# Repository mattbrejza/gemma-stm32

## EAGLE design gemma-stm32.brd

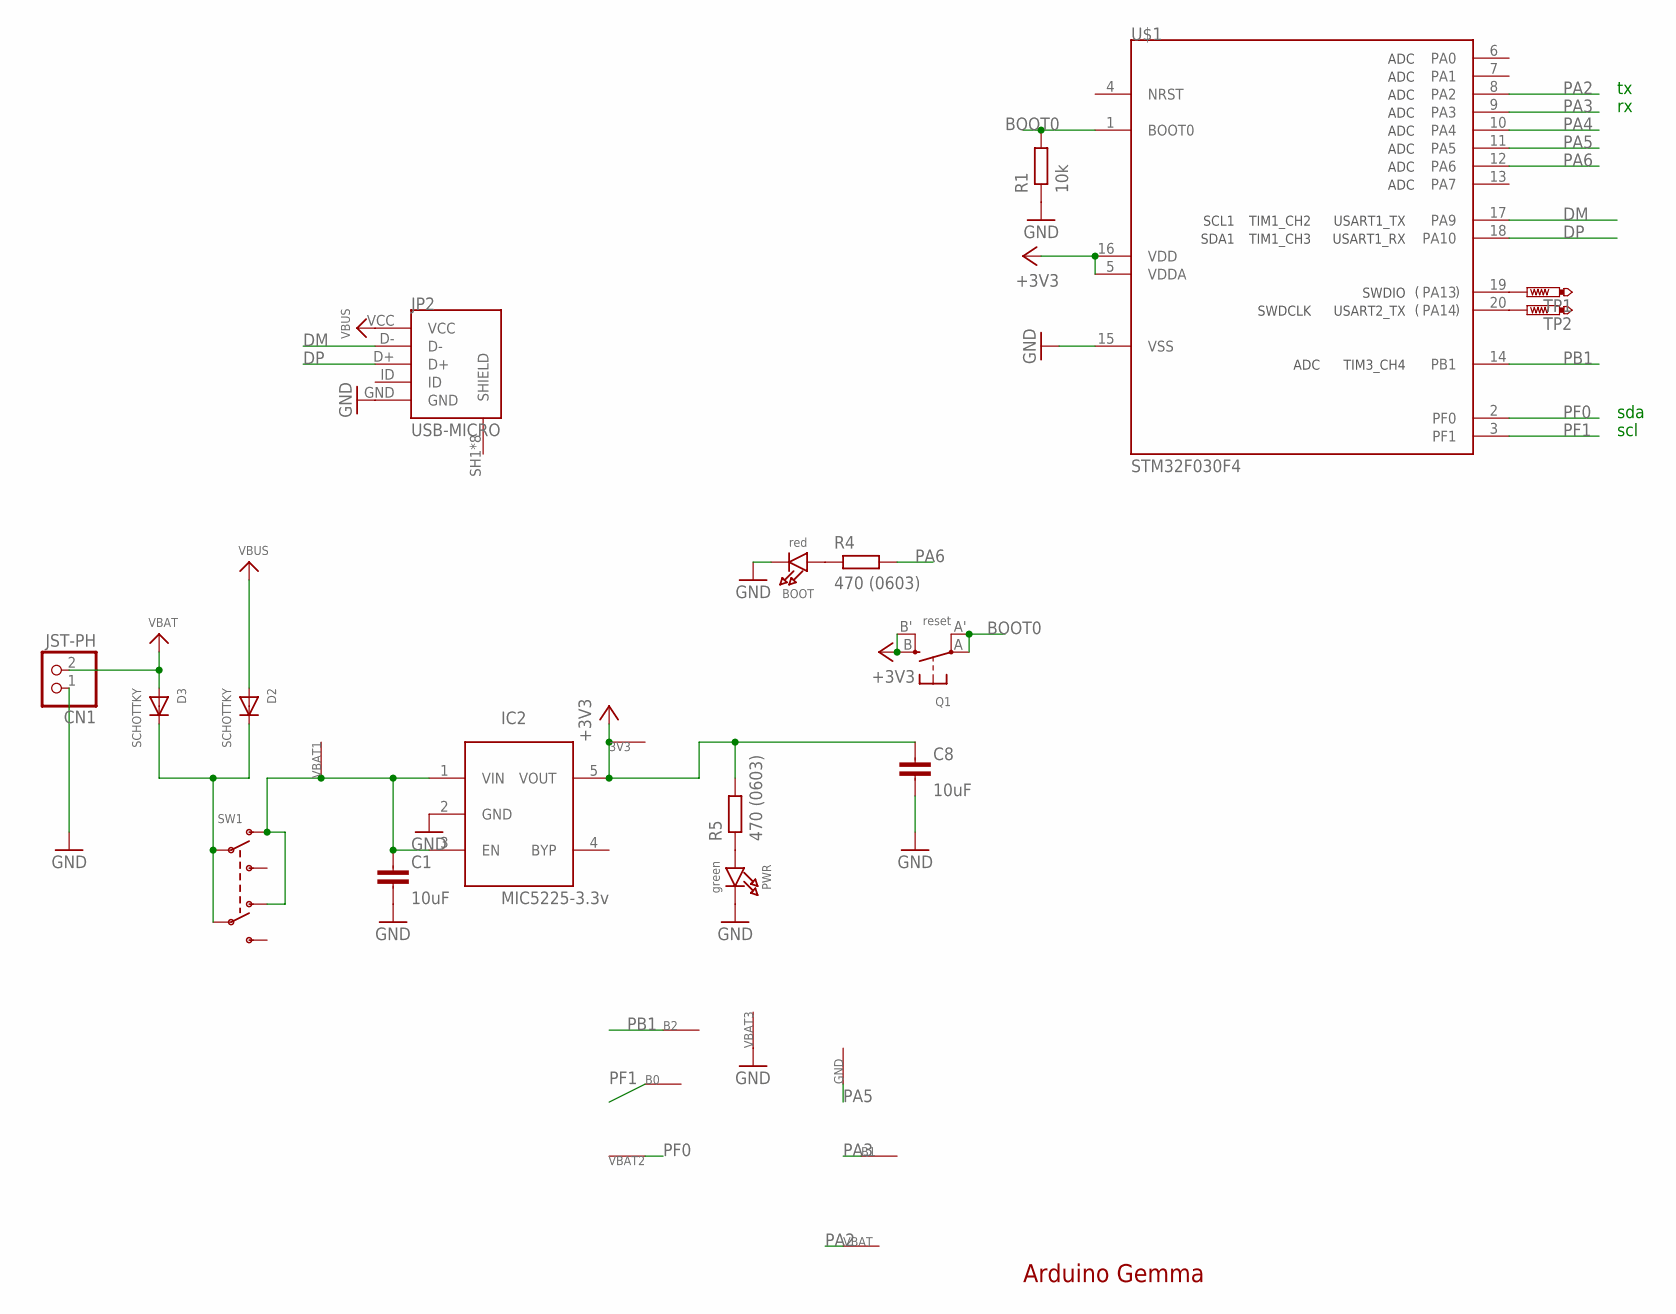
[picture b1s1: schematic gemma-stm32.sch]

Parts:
3V3: SEWTAP-2.0IN; SEWINGTAP_2.0
B0, B1: SEWTAP-2.0IN; SEWINGTAP_2.0
B2: SEWTAP2.0-L; SEWINGTAP_2.0_NARROW_L
BOOT: red; CHIPLED_0805_NOOUTLINE
C1, C8: 10uF; C0603-L
CN1: JST-PH; JSTPH2
D2, D3: SCHOTTKY; SOD-123FL
GND: SEWTAP-2.0IN; SEWINGTAP_2.0
IC2: MIC5225-3.3v; SOT23-5L
JP2: USB-MICRO; MOLEX_47589-0001
PWR: green; CHIPLED_0805_NOOUTLINE
Q1: reset; BTN_KMR2_4.6X2.8
R1: 10k; R0603-L
R4, R5: 470 (0603); R0603-L
SW1: SWITCH_DPDTEG1390; EG1390
TP1, TP2: PTR1TP08R; TP08R
U$1: STM32F030F4; TSSOP20
VBAT, VBAT2: SEWTAP-2.0IN; SEWINGTAP_2.0
VBAT1: SEWTAP; SEWINGTAP_2.0_ONESIDE
VBAT3: SEWTAP2.0-R; SEWINGTAP_2.0_NARROW_R

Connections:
+3V3: 3V3.P$1, C8.1, IC2.5 (VOUT), Q1.B (S), Q1.B' (S1), R5.2, U$1.5 (VDDA), U$1.16 (VDD)
BOOT0: Q1.A, Q1.A' (P1), R1.2, U$1.1 (BOOT0)
DM: JP2.D-, U$1.17 (PA9)
DP: JP2.D+, U$1.18 (PA10)
GND: BOOT.C, C1.2, C8.2, CN1.1, IC2.2 (GND), JP2.GND, PWR.C, R1.1, U$1.15 (VSS), VBAT3.P$1
unnamed: TP1.TP, U$1.19 (PA13)
unnamed: TP2.TP, U$1.20 (PA14)
unnamed: BOOT.A, R4.1
unnamed: C1.1, IC2.1 (VIN), IC2.3 (EN), SW1.O1, SW1.O2, VBAT1.P$1
unnamed: PWR.A, R5.1
unnamed: D2.C, D3.C, SW1.P1, SW1.P2
PA2: U$1.8 (PA2), VBAT.P$1
PA3: B1.P$1, U$1.9 (PA3)
PA4: U$1.10 (PA4)
PA5: GND.P$1, U$1.11 (PA5)
PA6: R4.2, U$1.12 (PA6)
PB1: B2.P$1, U$1.14 (PB1)
PF0: U$1.2 (PF0), VBAT2.P$1
PF1: B0.P$1, U$1.3 (PF1)
VBAT: CN1.2, D3.A
VBUS: D2.A, JP2.VCC

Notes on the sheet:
Arduino Gemma
sda
scl

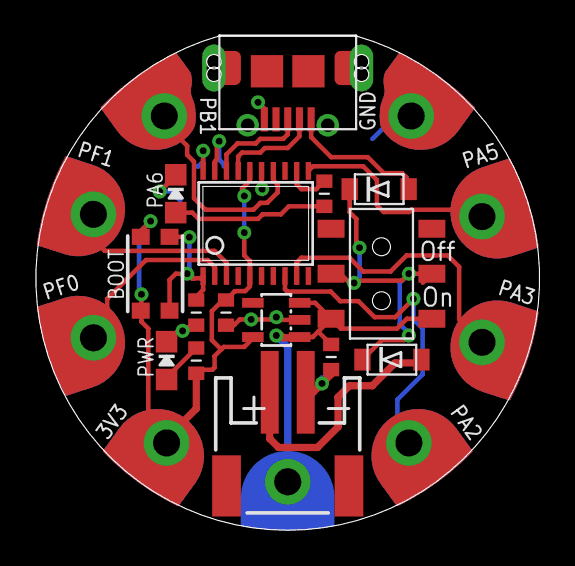
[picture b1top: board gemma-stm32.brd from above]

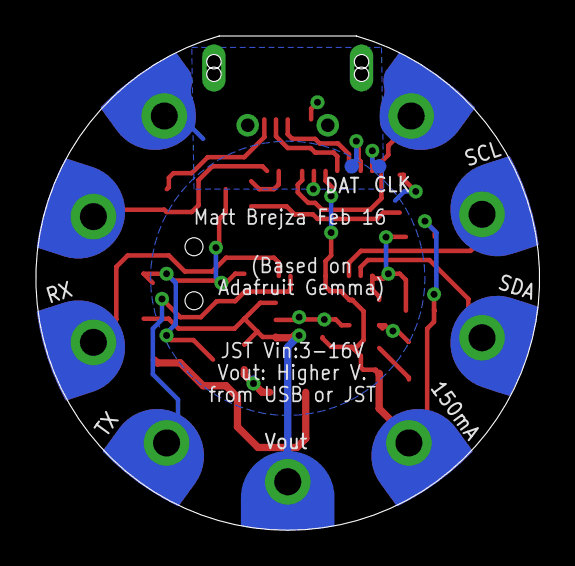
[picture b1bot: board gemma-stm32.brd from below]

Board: 2 copper layers, 28.0 x 27.5 mm, 26 parts (3 on the bottom side), 20 nets.

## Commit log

2016-02-15 inital commit
2016-02-15 adding pads lib

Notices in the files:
parts and their libraries:
microbuilder: This work is placed in the public domain, and may be freely used for commercial and non-commercial work with the following conditions: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
